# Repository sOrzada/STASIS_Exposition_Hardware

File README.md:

# STASIS_Exposure_Hardware
This is the repository for the exposure hardware of the STASIS project.
The corresponding software can be found in this repository: https://github.com/sOrzada/STASIS_Control

by Stephan Orzada @ German Cancer Research Center (DKFZ) 

# Overview
The STASIS RF exposure system is an open-source hardware and software platform designed for implant testing under exposure to radiofrequency (RF) fields, such as those encountered in the environment of an MRI system. For this purpose, the target RF frequency is 128 MHz, corresponding to the resonant frequency of protons in a 3 Tesla magnetic field. The system is capable of transmitting on eight independent RF channels, enabling parallel transmission.
To ensure the design is easily accessible to potential users, all design files and software are publicly available and can be accessed via the following repositories:
https://github.com/sOrzada/STASIS_Exposure_Hardware
https://github.com/sOrzada/STASIS_Control
All hardware components of the exposure system are licensed under the CERN-OHL-W while the software is licensed under a GNU GPL v3. In addition the project has been submitted to the conformity assessment body of the Open Source Imaging Initiative e.V. (https://www.opensourceimaging.org) to assess its open source status according to DIN SPEC 3105.  
To further improve accessibility, standard components with long production lifespans were selected wherever possible. For example, standard logic components were used instead of specialised microcontrollers or FPGAs.

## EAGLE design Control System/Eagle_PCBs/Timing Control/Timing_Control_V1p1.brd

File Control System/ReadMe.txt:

This Folder contains the PCBs and Housings for the Control System of the STASIS project's RF exposition system.
The PCBs are provided in two different formats: Eagle and KiCAD.
The Housings-folder contains .step files for the housings and front panels of the Eurocards.

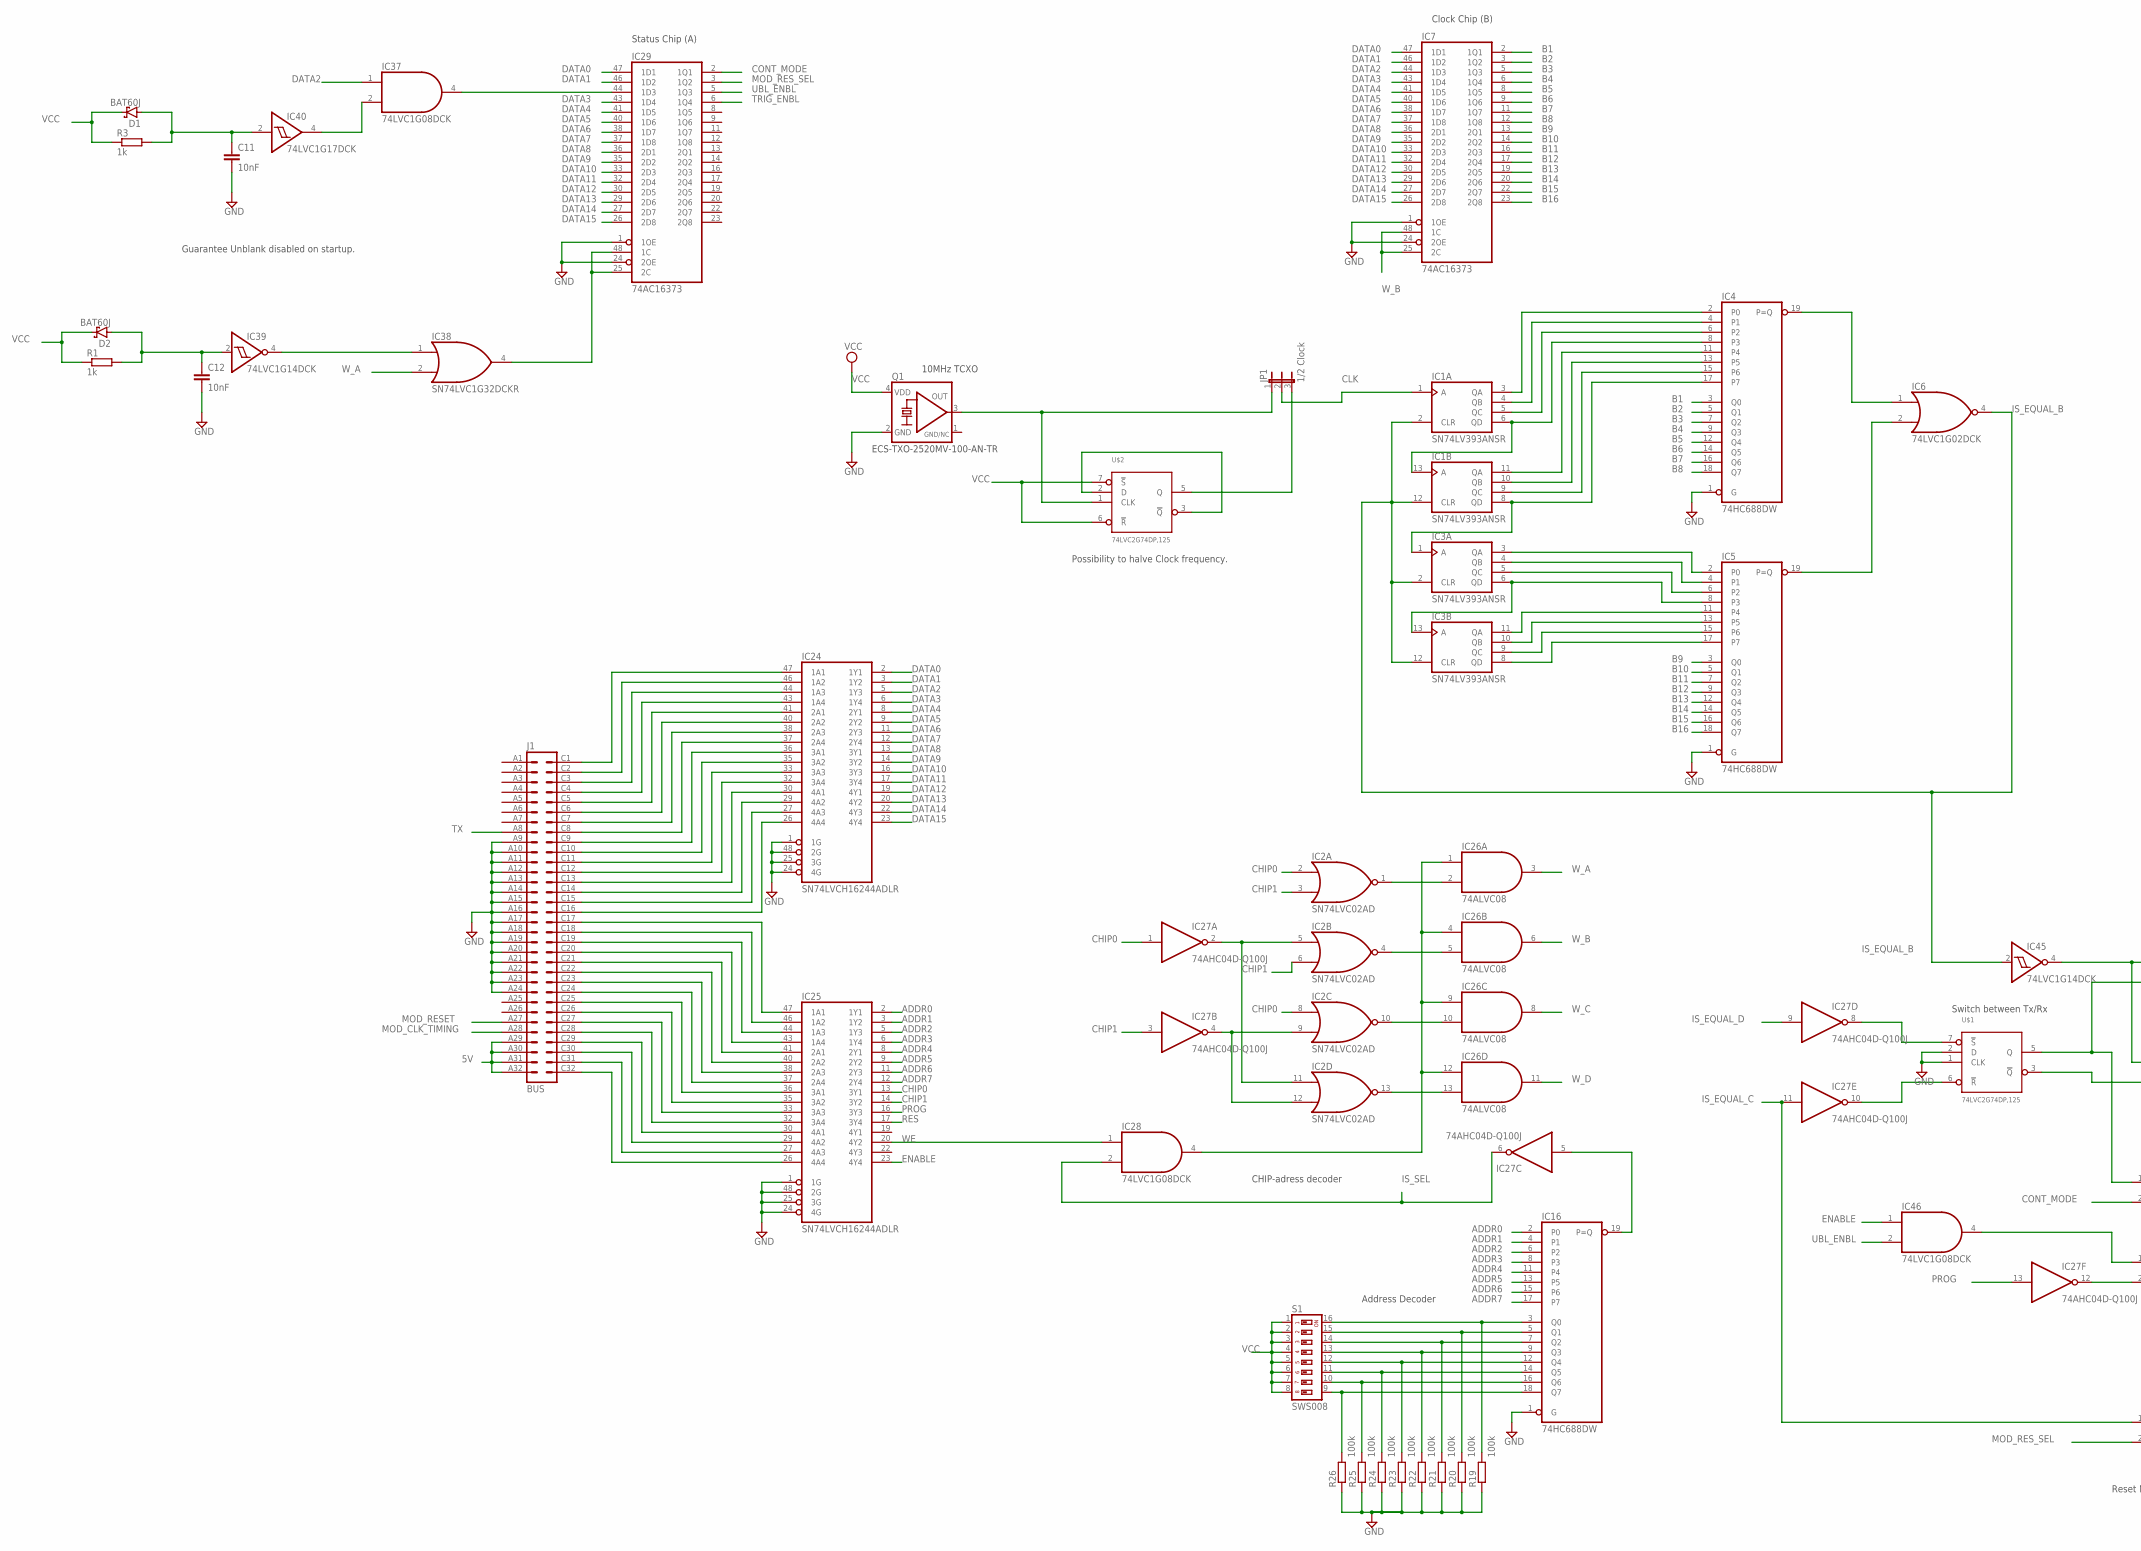
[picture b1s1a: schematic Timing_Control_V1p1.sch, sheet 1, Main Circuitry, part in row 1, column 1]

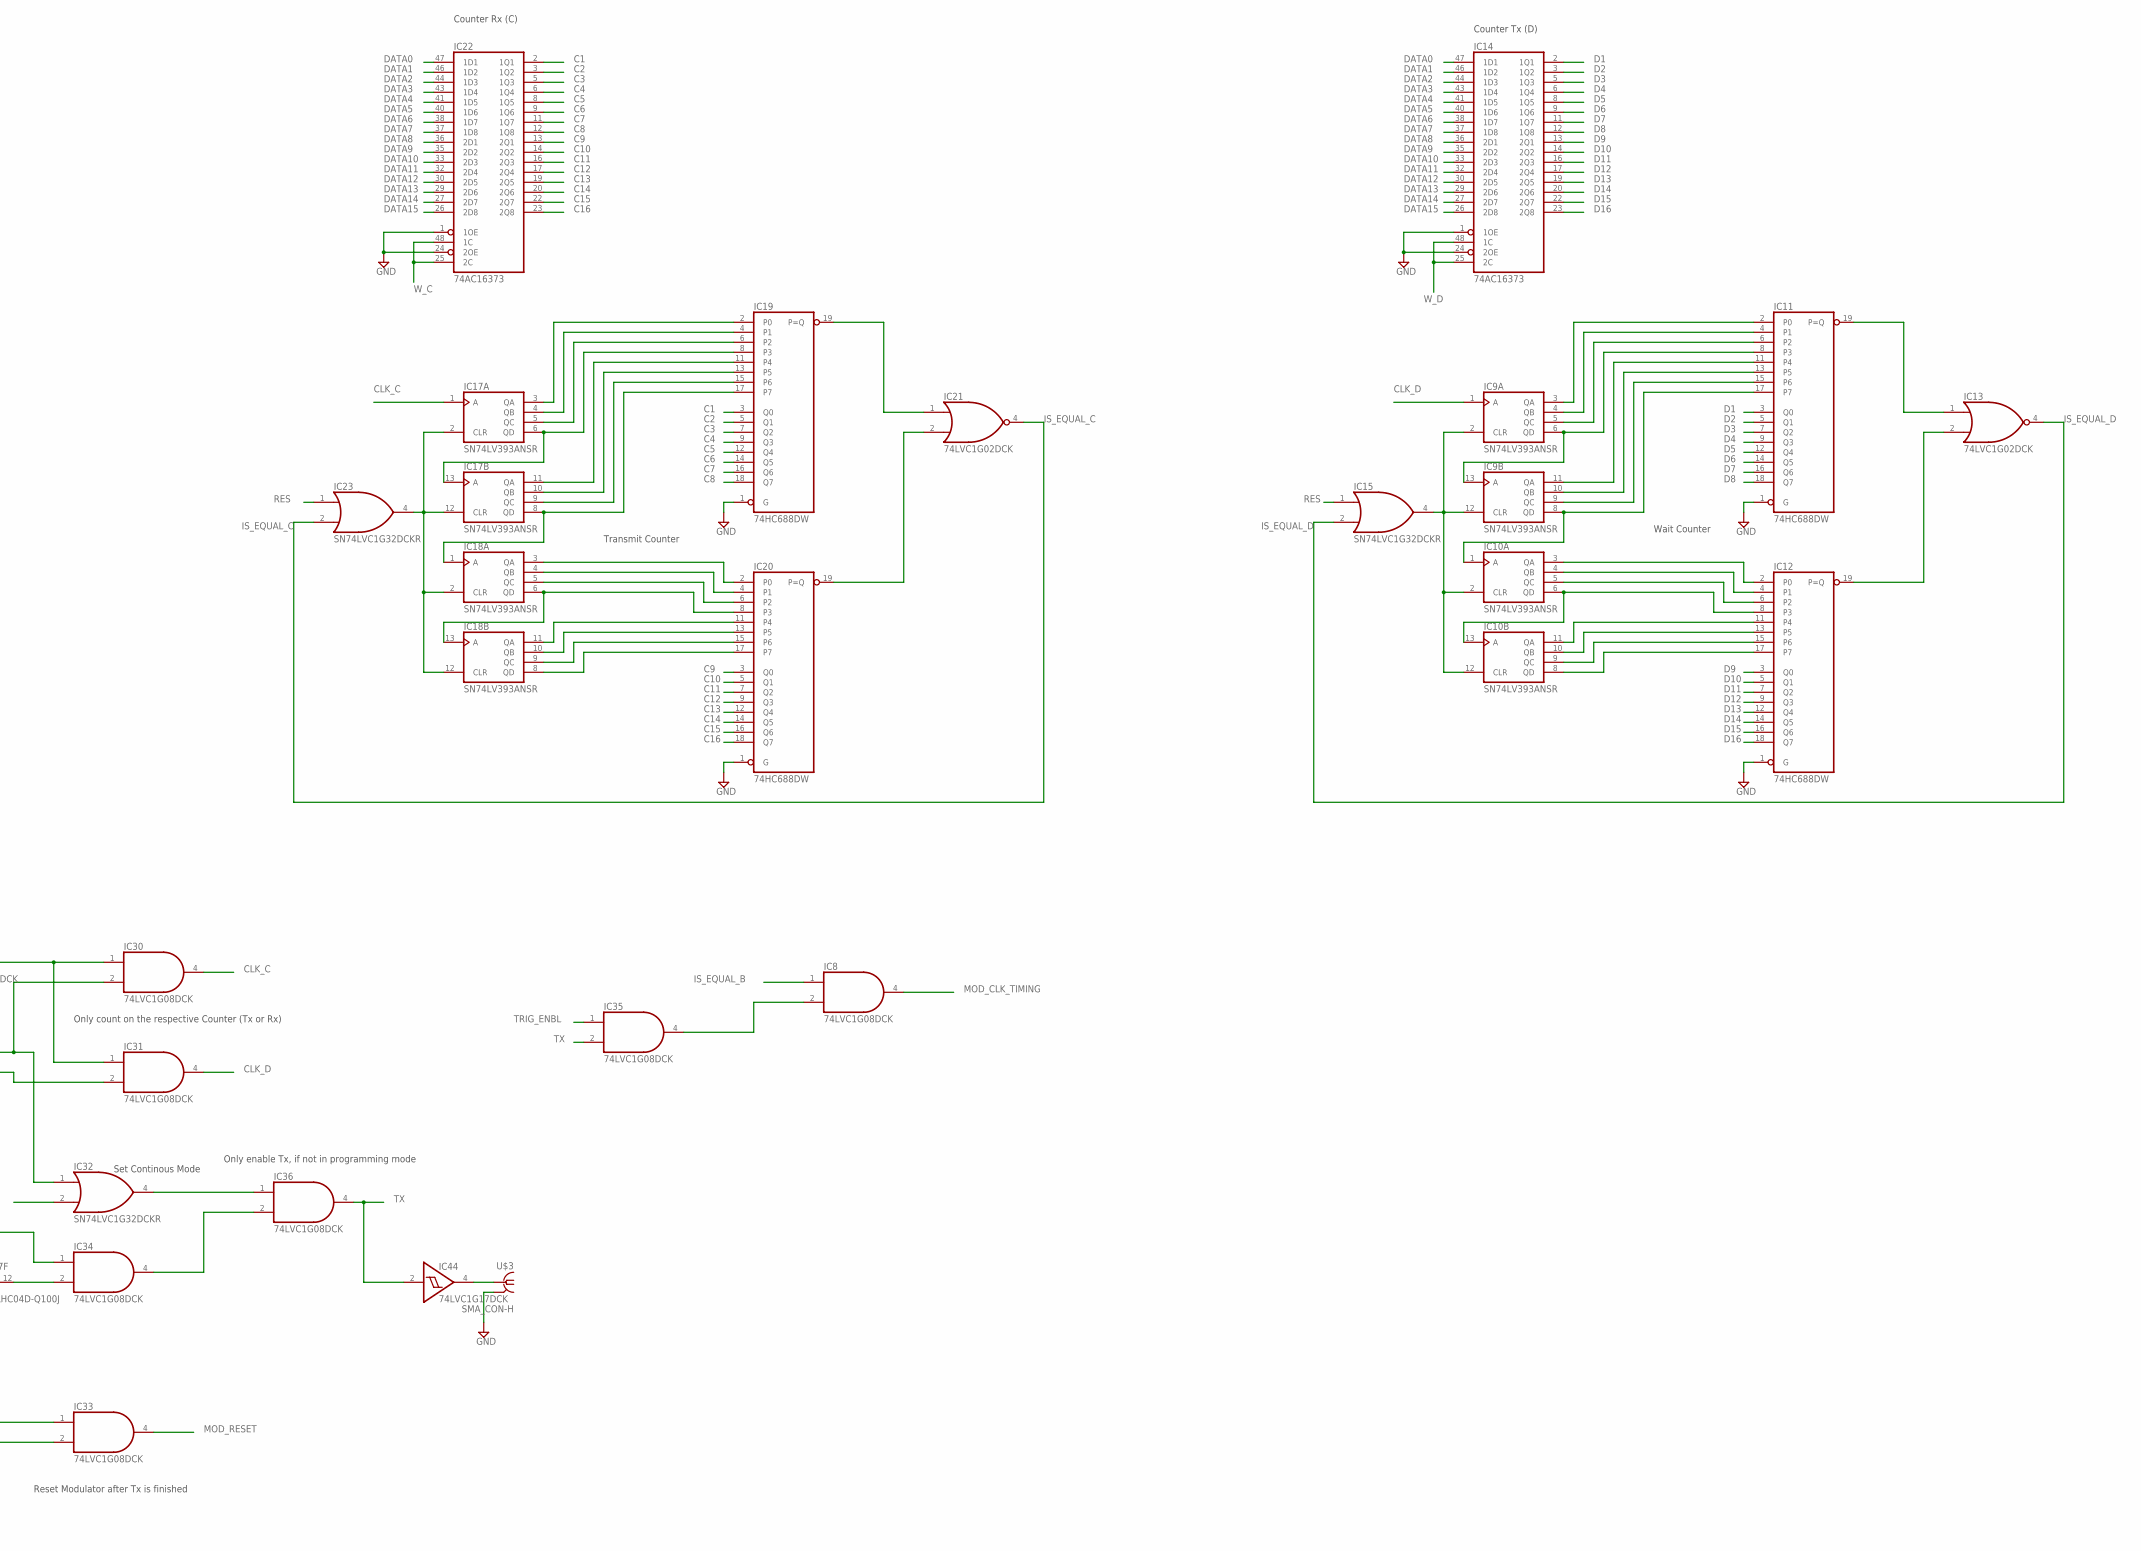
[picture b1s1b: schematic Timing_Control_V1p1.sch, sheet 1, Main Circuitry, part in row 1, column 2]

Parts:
C11, C12: 10nF; C0603
D1, D2: BAT60J; SOD323_ST
IC1, IC3, IC9, IC10, IC17, IC18: SN74LV393ANSR; SO14
IC2: SN74LVC02AD; SO14
IC4, IC5, IC11, IC12, IC16, IC19, IC20: 74HC688DW; SO20W
IC6, IC13, IC21: 74LVC1G02DCK; SC70-5
IC7, IC14, IC22, IC29: 74AC16373; SSOP48DL
IC8, IC28, IC30, IC31, IC33, IC34, IC35, IC36, IC37, IC46: 74LVC1G08DCK; SC70-5
IC15, IC23, IC32, IC38: SN74LVC1G32DCKR; SC70-5
IC24, IC25: SN74LVCH16244ADLR; SSOP48DL
IC26: 74ALVC08; SO14
IC27: 74AHC04D-Q100J; SO14
IC39, IC45: 74LVC1G14DCK; SC70-5
IC40, IC44: 74LVC1G17DCK; SC70-5
J1: BUS; VG64P
JP1: 1/2 Clock; JP2
Q1: ECS-TXO-2520MV-100-AN-TR; 2.5X2.0_KXO-86-TCXO
R1, R3: 1k; R0603
R19, R20, R21, R22, R23, R24, R25, R26: 100k; R0603
S1: SWS008; SMS-008
U$1, U$2: 74LVC2G74DP,125; SSOP08
U$3: SMA_CON-H; BU-SMA-H

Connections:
5V: J1.A29, J1.A30, J1.A31, J1.A32; also elsewhere on the board
ADDR0: IC16.2 (P0), IC25.2 (1Y1)
ADDR1: IC16.4 (P1), IC25.3 (1Y2)
ADDR2: IC16.6 (P2), IC25.5 (1Y3)
ADDR3: IC16.8 (P3), IC25.6 (1Y4)
ADDR4: IC16.11 (P4), IC25.8 (2Y1)
ADDR5: IC16.13 (P5), IC25.9 (2Y2)
ADDR6: IC16.15 (P6), IC25.11 (2Y3)
ADDR7: IC16.17 (P7), IC25.12 (2Y4)
B1: IC4.3 (Q0), IC7.2 (1Q1)
B2: IC4.5 (Q1), IC7.3 (1Q2)
B3: IC4.7 (Q2), IC7.5 (1Q3)
B4: IC4.9 (Q3), IC7.6 (1Q4)
B5: IC4.12 (Q4), IC7.8 (1Q5)
B6: IC4.14 (Q5), IC7.9 (1Q6)
B7: IC4.16 (Q6), IC7.11 (1Q7)
B8: IC4.18 (Q7), IC7.12 (1Q8)
B9: IC5.3 (Q0), IC7.13 (2Q1)
B10: IC5.5 (Q1), IC7.14 (2Q2)
B11: IC5.7 (Q2), IC7.16 (2Q3)
B12: IC5.9 (Q3), IC7.17 (2Q4)
B13: IC5.12 (Q4), IC7.19 (2Q5)
B14: IC5.14 (Q5), IC7.20 (2Q6)
B15: IC5.16 (Q6), IC7.22 (2Q7)
B16: IC5.18 (Q7), IC7.23 (2Q8)
C1: IC19.3 (Q0), IC22.2 (1Q1)
C2: IC19.5 (Q1), IC22.3 (1Q2)
C3: IC19.7 (Q2), IC22.5 (1Q3)
C4: IC19.9 (Q3), IC22.6 (1Q4)
C5: IC19.12 (Q4), IC22.8 (1Q5)
C6: IC19.14 (Q5), IC22.9 (1Q6)
C7: IC19.16 (Q6), IC22.11 (1Q7)
C8: IC19.18 (Q7), IC22.12 (1Q8)
C9: IC20.3 (Q0), IC22.13 (2Q1)
C10: IC20.5 (Q1), IC22.14 (2Q2)
C11: IC20.7 (Q2), IC22.16 (2Q3)
C12: IC20.9 (Q3), IC22.17 (2Q4)
C13: IC20.12 (Q4), IC22.19 (2Q5)
C14: IC20.14 (Q5), IC22.20 (2Q6)
C15: IC20.16 (Q6), IC22.22 (2Q7)
C16: IC20.18 (Q7), IC22.23 (2Q8)
CHIP0: IC2.2 (I0), IC2.8 (I0), IC25.13 (3Y1), IC27.1 (I)
CHIP1: IC2.3 (I1), IC2.6 (I1), IC25.14 (3Y2), IC27.3 (I)
CLK: IC1.1 (A), JP1.2
CLK_C: IC17.1 (A), IC30.4 (O)
CLK_D: IC9.1 (A), IC31.4 (O)
CLR1: IC9.2 (CLR), IC9.12 (CLR), IC10.2 (CLR), IC10.12 (CLR), IC15.4 (O)
CLR2: IC17.2 (CLR), IC17.12 (CLR), IC18.2 (CLR), IC18.12 (CLR), IC23.4 (O)
CONT_MODE: IC29.2 (1Q1), IC32.2 (I1); also elsewhere on the board
D1: IC11.3 (Q0), IC14.2 (1Q1)
D2: IC11.5 (Q1), IC14.3 (1Q2)
D3: IC11.7 (Q2), IC14.5 (1Q3)
D4: IC11.9 (Q3), IC14.6 (1Q4)
D5: IC11.12 (Q4), IC14.8 (1Q5)
D6: IC11.14 (Q5), IC14.9 (1Q6)
D7: IC11.16 (Q6), IC14.11 (1Q7)
D8: IC11.18 (Q7), IC14.12 (1Q8)
D9: IC12.3 (Q0), IC14.13 (2Q1)
D10: IC12.5 (Q1), IC14.14 (2Q2)
D11: IC12.7 (Q2), IC14.16 (2Q3)
D12: IC12.9 (Q3), IC14.17 (2Q4)
D13: IC12.12 (Q4), IC14.19 (2Q5)
D14: IC12.14 (Q5), IC14.20 (2Q6)
D15: IC12.16 (Q6), IC14.22 (2Q7)
D16: IC12.18 (Q7), IC14.23 (2Q8)
DATA0: IC7.47 (1D1), IC14.47 (1D1), IC22.47 (1D1), IC24.2 (1Y1), IC29.47 (1D1)
DATA1: IC7.46 (1D2), IC14.46 (1D2), IC22.46 (1D2), IC24.3 (1Y2), IC29.46 (1D2)
DATA2: IC7.44 (1D3), IC14.44 (1D3), IC22.44 (1D3), IC24.5 (1Y3), IC37.1 (I0)
DATA3: IC7.43 (1D4), IC14.43 (1D4), IC22.43 (1D4), IC24.6 (1Y4), IC29.43 (1D4)
DATA4: IC7.41 (1D5), IC14.41 (1D5), IC22.41 (1D5), IC24.8 (2Y1), IC29.41 (1D5)
DATA5: IC7.40 (1D6), IC14.40 (1D6), IC22.40 (1D6), IC24.9 (2Y2), IC29.40 (1D6)
DATA6: IC7.38 (1D7), IC14.38 (1D7), IC22.38 (1D7), IC24.11 (2Y3), IC29.38 (1D7)
DATA7: IC7.37 (1D8), IC14.37 (1D8), IC22.37 (1D8), IC24.12 (2Y4), IC29.37 (1D8)
DATA8: IC7.36 (2D1), IC14.36 (2D1), IC22.36 (2D1), IC24.13 (3Y1), IC29.36 (2D1)
DATA9: IC7.35 (2D2), IC14.35 (2D2), IC22.35 (2D2), IC24.14 (3Y2), IC29.35 (2D2)
DATA10: IC7.33 (2D3), IC14.33 (2D3), IC22.33 (2D3), IC24.16 (3Y3), IC29.33 (2D3)
DATA11: IC7.32 (2D4), IC14.32 (2D4), IC22.32 (2D4), IC24.17 (3Y4), IC29.32 (2D4)
DATA12: IC7.30 (2D5), IC14.30 (2D5), IC22.30 (2D5), IC24.19 (4Y1), IC29.30 (2D5)
DATA13: IC7.29 (2D6), IC14.29 (2D6), IC22.29 (2D6), IC24.20 (4Y2), IC29.29 (2D6)
DATA14: IC7.27 (2D7), IC14.27 (2D7), IC22.27 (2D7), IC24.22 (4Y3), IC29.27 (2D7)
DATA15: IC7.26 (2D8), IC14.26 (2D8), IC22.26 (2D8), IC24.23 (4Y4), IC29.26 (2D8)
ENABLE: IC25.23 (4Y4), IC46.1 (I0)
GND: C11.2, C12.2, IC1.7 (GND), IC2.7 (GND), IC3.7 (GND), IC4.1 (G), IC4.10 (GND), IC5.1 (G), IC5.10 (GND), IC6.3 (GND), IC7.1 (1OE), IC7.4 (GND), IC7.10 (GND), IC7.15 (GND), IC7.21 (GND), IC7.24 (2OE), IC7.28 (GND), IC7.34 (GND), IC7.39 (GND), IC7.45 (GND), IC8.3 (GND), IC9.7 (GND), IC10.7 (GND), IC11.1 (G), IC11.10 (GND), IC12.1 (G), IC12.10 (GND), IC13.3 (GND), IC14.1 (1OE), IC14.4 (GND), IC14.10 (GND), IC14.15 (GND), IC14.21 (GND), IC14.24 (2OE), IC14.28 (GND), IC14.34 (GND), IC14.39 (GND), IC14.45 (GND), IC15.3 (GND), IC16.1 (G), IC16.10 (GND), IC17.7 (GND), IC18.7 (GND), IC19.1 (G), IC19.10 (GND), IC20.1 (G), IC20.10 (GND), IC21.3 (GND), IC22.1 (1OE), IC22.4 (GND), IC22.10 (GND), IC22.15 (GND), IC22.21 (GND), IC22.24 (2OE), IC22.28 (GND), IC22.34 (GND), IC22.39 (GND), IC22.45 (GND), IC23.3 (GND), IC24.1 (1G), IC24.4 (GND), IC24.10 (GND), IC24.15 (GND), IC24.21 (GND), IC24.24 (4G), IC24.25 (3G), IC24.28 (GND), IC24.34 (GND), IC24.39 (GND), IC24.45 (GND), IC24.48 (2G), IC25.1 (1G), IC25.4 (GND), IC25.10 (GND), IC25.15 (GND), IC25.21 (GND), IC25.24 (4G), IC25.25 (3G), IC25.28 (GND), IC25.34 (GND), IC25.39 (GND), IC25.45 (GND), IC25.48 (2G), IC26.7 (GND), IC27.7 (GND), IC28.3 (GND), IC29.1 (1OE), IC29.4 (GND), IC29.10 (GND), IC29.15 (GND), IC29.21 (GND), IC29.24 (2OE), IC29.28 (GND), IC29.34 (GND), IC29.39 (GND), IC29.45 (GND), IC30.3 (GND), IC31.3 (GND), IC32.3 (GND), IC33.3 (GND), IC34.3 (GND), IC35.3 (GND), IC36.3 (GND), IC37.3 (GND), IC38.3 (GND), IC39.3 (GND), IC40.3 (GND), IC44.3 (GND), IC45.3 (GND), IC46.3 (GND), J1.A9, J1.A10, J1.A11, J1.A12, J1.A13, J1.A14, J1.A15, J1.A16, J1.A17, J1.A18, J1.A19, J1.A20, J1.A21, J1.A22, J1.A23, J1.A24, Q1.2 (GND), R19.1, R20.1, R21.1, R22.1, R23.1, R24.1, R25.1, R26.1, U$1.1 (CLK), U$1.2 (D), U$1.4 (GND), U$2.4 (GND), U$3.2 (GND), U$3.3 (GND), U$3.4 (GND), U$3.5 (GND); also elsewhere on the board
GND/NC: Q1.1 (GND/NC)
IS_EQUAL_B: IC1.2 (CLR), IC1.12 (CLR), IC3.2 (CLR), IC3.12 (CLR), IC6.4 (O), IC8.1 (I0), IC45.2 (I)
IS_EQUAL_C: IC21.4 (O), IC23.2 (I1), IC27.11 (I), IC33.1 (I0)
IS_EQUAL_D: IC13.4 (O), IC15.2 (I1), IC27.9 (I)
IS_SEL: IC27.6 (O), IC28.2 (I1); also elsewhere on the board
MOD_CLK_TIMING: IC8.4 (O), J1.A28
MOD_RESET: IC33.4 (O), J1.A27
MOD_RES_SEL: IC29.3 (1Q2), IC33.2 (I1)
unnamed: IC1.6 (QD), IC1.13 (A), IC4.8 (P3)
unnamed: IC1.8 (QD), IC3.1 (A), IC4.17 (P7)
unnamed: IC3.6 (QD), IC3.13 (A), IC5.8 (P3)
unnamed: IC8.2 (I1), IC35.4 (O)
unnamed: IC1.3 (QA), IC4.2 (P0)
unnamed: IC1.4 (QB), IC4.4 (P1)
unnamed: IC1.5 (QC), IC4.6 (P2)
unnamed: IC1.11 (QA), IC4.11 (P4)
unnamed: IC1.10 (QB), IC4.13 (P5)
unnamed: IC1.9 (QC), IC4.15 (P6)
unnamed: IC3.3 (QA), IC5.2 (P0)
unnamed: IC3.4 (QB), IC5.4 (P1)
unnamed: IC3.5 (QC), IC5.6 (P2)
unnamed: IC9.6 (QD), IC9.13 (A), IC11.8 (P3)
unnamed: IC3.11 (QA), IC5.11 (P4)
unnamed: IC3.10 (QB), IC5.13 (P5)
unnamed: IC3.9 (QC), IC5.15 (P6)
unnamed: IC3.8 (QD), IC5.17 (P7)
unnamed: IC4.19 (P=Q), IC6.1 (I0)
unnamed: IC5.19 (P=Q), IC6.2 (I1)
unnamed: IC9.8 (QD), IC10.1 (A), IC11.17 (P7)
unnamed: IC10.6 (QD), IC10.13 (A), IC12.8 (P3)
unnamed: IC9.3 (QA), IC11.2 (P0)
unnamed: IC9.4 (QB), IC11.4 (P1)
unnamed: IC9.5 (QC), IC11.6 (P2)
unnamed: IC9.11 (QA), IC11.11 (P4)
unnamed: IC9.10 (QB), IC11.13 (P5)
unnamed: IC9.9 (QC), IC11.15 (P6)
unnamed: IC10.3 (QA), IC12.2 (P0)
unnamed: IC10.4 (QB), IC12.4 (P1)
unnamed: IC10.5 (QC), IC12.6 (P2)
unnamed: IC10.11 (QA), IC12.11 (P4)
unnamed: IC10.10 (QB), IC12.13 (P5)
unnamed: IC10.9 (QC), IC12.15 (P6)
unnamed: IC10.8 (QD), IC12.17 (P7)
unnamed: IC11.19 (P=Q), IC13.1 (I0)
unnamed: IC12.19 (P=Q), IC13.2 (I1)
unnamed: IC27.12 (O), IC34.2 (I1)
unnamed: IC17.6 (QD), IC17.13 (A), IC19.8 (P3)
unnamed: IC16.3 (Q0), R19.2, S1.16
unnamed: IC17.8 (QD), IC18.1 (A), IC19.17 (P7)
unnamed: IC18.6 (QD), IC18.13 (A), IC20.8 (P3)
unnamed: IC17.3 (QA), IC19.2 (P0)
unnamed: IC17.4 (QB), IC19.4 (P1)
unnamed: IC17.5 (QC), IC19.6 (P2)
unnamed: IC17.11 (QA), IC19.11 (P4)
unnamed: IC17.10 (QB), IC19.13 (P5)
unnamed: IC17.9 (QC), IC19.15 (P6)
unnamed: IC18.3 (QA), IC20.2 (P0)
unnamed: IC18.4 (QB), IC20.4 (P1)
unnamed: IC18.5 (QC), IC20.6 (P2)
unnamed: IC18.11 (QA), IC20.11 (P4)
unnamed: IC18.10 (QB), IC20.13 (P5)
unnamed: IC18.9 (QC), IC20.15 (P6)
unnamed: IC18.8 (QD), IC20.17 (P7)
unnamed: IC19.19 (P=Q), IC21.1 (I0)
unnamed: IC20.19 (P=Q), IC21.2 (I1)
unnamed: IC34.4 (O), IC36.2 (I1)
unnamed: IC24.47 (1A1), J1.C1
unnamed: IC24.46 (1A2), J1.C2
unnamed: IC24.44 (1A3), J1.C3
unnamed: IC24.43 (1A4), J1.C4
unnamed: IC24.41 (2A1), J1.C5
unnamed: IC16.5 (Q1), R20.2, S1.15
unnamed: IC16.7 (Q2), R21.2, S1.14
unnamed: IC16.9 (Q3), R22.2, S1.13
unnamed: IC16.12 (Q4), R23.2, S1.12
unnamed: IC16.14 (Q5), R24.2, S1.11
unnamed: IC16.16 (Q6), R25.2, S1.10
unnamed: IC16.18 (Q7), R26.2, S1.9
unnamed: IC24.40 (2A2), J1.C6
unnamed: IC24.38 (2A3), J1.C7
unnamed: IC24.37 (2A4), J1.C8
unnamed: IC24.36 (3A1), J1.C9
unnamed: IC24.35 (3A2), J1.C10
unnamed: IC24.33 (3A3), J1.C11
unnamed: IC24.32 (3A4), J1.C12
unnamed: IC24.30 (4A1), J1.C13
unnamed: IC24.29 (4A2), J1.C14
unnamed: IC16.19 (P=Q), IC27.5 (I)
unnamed: IC24.27 (4A3), J1.C15
unnamed: IC24.26 (4A4), J1.C16
unnamed: IC25.47 (1A1), J1.C17
unnamed: IC25.46 (1A2), J1.C18
unnamed: IC25.44 (1A3), J1.C19
unnamed: IC25.43 (1A4), J1.C20
unnamed: IC25.41 (2A1), J1.C21
unnamed: IC25.40 (2A2), J1.C22
unnamed: IC25.38 (2A3), J1.C23
unnamed: IC25.37 (2A4), J1.C24
unnamed: IC25.36 (3A1), J1.C25
unnamed: IC25.35 (3A2), J1.C26
unnamed: IC25.33 (3A3), J1.C27
unnamed: IC25.32 (3A4), J1.C28
unnamed: IC25.30 (4A1), J1.C29
unnamed: IC25.29 (4A2), J1.C30
unnamed: IC25.27 (4A3), J1.C31
unnamed: IC25.26 (4A4), J1.C32
unnamed: IC2.5 (I0), IC2.11 (I0), IC27.2 (O)
unnamed: IC2.9 (I1), IC2.12 (I1), IC27.4 (O)
unnamed: IC2.1 (O), IC26.2 (I1)
unnamed: IC2.4 (O), IC26.5 (I1)
unnamed: IC2.10 (O), IC26.10 (I1)
unnamed: IC2.13 (O), IC26.13 (I1)
unnamed: IC26.1 (I0), IC26.4 (I0), IC26.9 (I0), IC26.12 (I0), IC28.4 (O)
unnamed: IC30.2 (I1), IC32.1 (I0), U$1.5 (Q)
unnamed: IC31.2 (I1), U$1.3 (!Q)
unnamed: IC27.8 (O), U$1.7 (!S)
unnamed: IC27.10 (O), U$1.6 (!R)
unnamed: IC32.4 (O), IC36.1 (I0)
unnamed: JP1.1, Q1.3 (OUT), U$2.1 (CLK)
unnamed: IC29.44 (1D3), IC37.4 (O)
unnamed: U$2.2 (D), U$2.3 (!Q)
unnamed: JP1.3, U$2.5 (Q)
unnamed: IC29.25 (2C), IC29.48 (1C), IC38.4 (O)
unnamed: IC37.2 (I1), IC40.4 (O)
unnamed: C11.1, D1.A, IC40.2 (I), R3.2
unnamed: IC38.1 (I0), IC39.4 (O)
unnamed: C12.1, D2.A, IC39.2 (I), R1.2
unnamed: IC34.1 (I0), IC46.4 (O)
unnamed: IC44.4 (O), U$3.1
unnamed: IC30.1 (I0), IC31.1 (I0), IC45.4 (O)
PROG: IC25.16 (3Y3), IC27.13 (I)
RES: IC15.1 (I0), IC23.1 (I0), IC25.17 (3Y4)
TRIG_ENBL: IC29.6 (1Q4), IC35.1 (I0)
TX: IC35.2 (I1), IC36.4 (O), IC44.2 (I), J1.A8; also elsewhere on the board
UBL_ENBL: IC29.5 (1Q3), IC46.2 (I1)
VCC: D1.C, D2.C, IC1.14 (VCC), IC2.14 (VCC), IC3.14 (VCC), IC4.20 (VCC), IC5.20 (VCC), IC6.5 (VCC), IC7.7 (VCC), IC7.18 (VCC), IC7.31 (VCC), IC7.42 (VCC), IC8.5 (VCC), IC9.14 (VCC), IC10.14 (VCC), IC11.20 (VCC), IC12.20 (VCC), IC13.5 (VCC), IC14.7 (VCC), IC14.18 (VCC), IC14.31 (VCC), IC14.42 (VCC), IC15.5 (VCC), IC16.20 (VCC), IC17.14 (VCC), IC18.14 (VCC), IC19.20 (VCC), IC20.20 (VCC), IC21.5 (VCC), IC22.7 (VCC), IC22.18 (VCC), IC22.31 (VCC), IC22.42 (VCC), IC23.5 (VCC), IC24.7 (VCC), IC24.18 (VCC), IC24.31 (VCC), IC24.42 (VCC), IC25.7 (VCC), IC25.18 (VCC), IC25.31 (VCC), IC25.42 (VCC), IC26.14 (VCC), IC27.14 (VCC), IC28.5 (VCC), IC29.7 (VCC), IC29.18 (VCC), IC29.31 (VCC), IC29.42 (VCC), IC30.5 (VCC), IC31.5 (VCC), IC32.5 (VCC), IC33.5 (VCC), IC34.5 (VCC), IC35.5 (VCC), IC36.5 (VCC), IC37.5 (VCC), IC38.5 (VCC), IC39.5 (VCC), IC40.5 (VCC), IC44.5 (VCC), IC45.5 (VCC), IC46.5 (VCC), Q1.4 (VDD), R1.1, R3.1, S1.1, S1.2, S1.3, S1.4, S1.5, S1.6, S1.7, S1.8, U$1.8 (VCC), U$2.6 (!R), U$2.7 (!S), U$2.8 (VCC); also elsewhere on the board
WE: IC25.20 (4Y2), IC28.1 (I0)
W_A: IC26.3 (O), IC38.2 (I1)
W_B: IC7.25 (2C), IC7.48 (1C), IC26.6 (O)
W_C: IC22.25 (2C), IC22.48 (1C), IC26.8 (O)
W_D: IC14.25 (2C), IC14.48 (1C), IC26.11 (O)

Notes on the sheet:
Address Decoder
CHIP-adress decoder
Status Chip (A)
Clock Chip (B)
Counter Tx (D)
Counter Rx (C)
Reset Modulator after Tx is finished
Set Continous Mode
Switch between Tx/Rx
Only count on the respective Counter (Tx or Rx)
Only enable Tx, if not in programming mode
ECS-TXO-2520MV-100-AN-TR
10MHz TCXO
Possibility to halve Clock frequency.
Guarantee Unblank disabled on startup.
Transmit Counter
Wait Counter

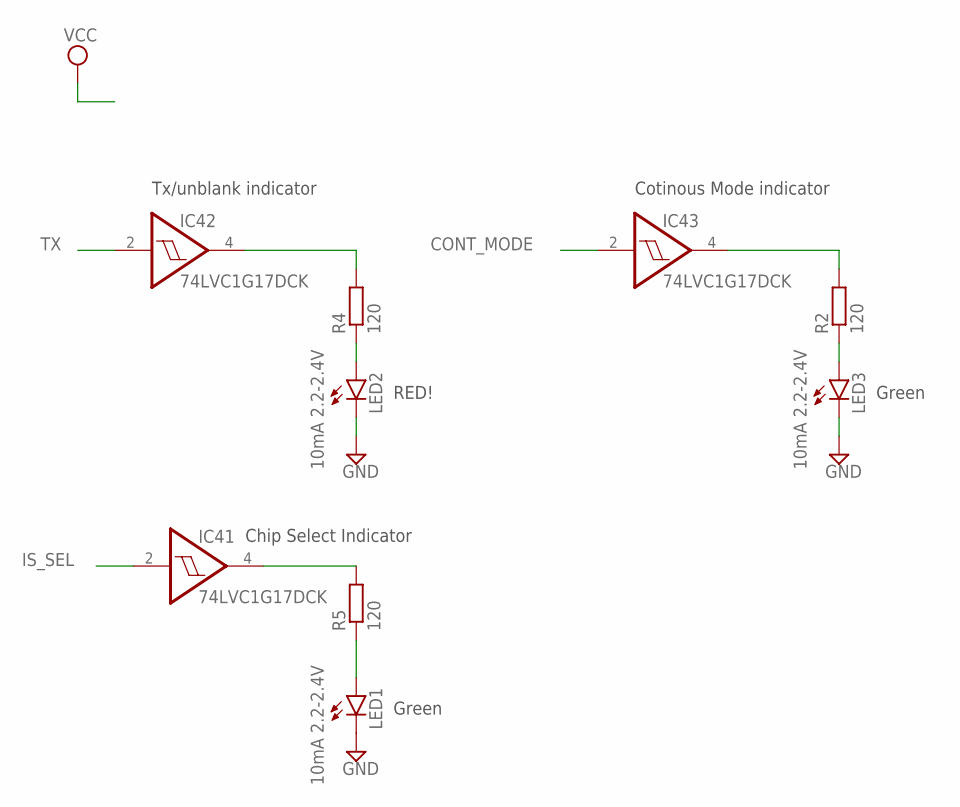
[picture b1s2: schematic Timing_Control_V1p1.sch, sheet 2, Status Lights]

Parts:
IC41, IC42, IC43: 74LVC1G17DCK; SC70-5
LED1, LED2, LED3: 10mA 2.2-2.4V; LED3MM
R2, R4, R5: 120; R0603

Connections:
CONT_MODE: IC43.2 (I); also elsewhere on the board
GND: IC41.3 (GND), IC42.3 (GND), IC43.3 (GND), LED1.K (C), LED2.K (C), LED3.K (C); also elsewhere on the board
IS_SEL: IC41.2 (I); also elsewhere on the board
unnamed: IC43.4 (O), R2.2
unnamed: IC41.4 (O), R5.2
unnamed: LED1.A, R5.1
unnamed: LED3.A, R2.1
unnamed: IC42.4 (O), R4.2
unnamed: LED2.A, R4.1
TX: IC42.2 (I); also elsewhere on the board
VCC: IC41.5 (VCC), IC42.5 (VCC), IC43.5 (VCC); also elsewhere on the board

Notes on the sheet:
Chip Select Indicator
RED!
Green
Tx/unblank indicator
Cotinous Mode indicator

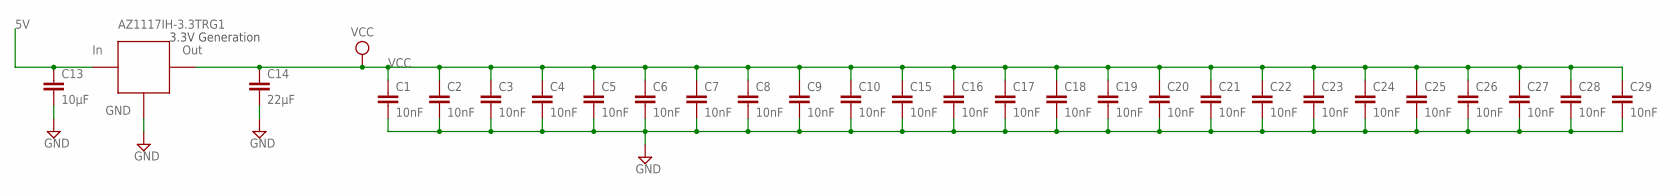
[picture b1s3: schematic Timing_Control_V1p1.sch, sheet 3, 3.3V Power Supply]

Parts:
C1, C2, C3, C4, C5, C6, C7, C8, C9, C10, C15, C16, C17, C18, C19, C20, C21, C22, C23, C24, C25, C26, C27, C28, C29: 10nF; C0603
C13: 10µF; C1206
C14: 22µF; C1206
U$9: AZ1117IH-3.3TRG1; SOT223

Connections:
5V: C13.1, U$9.3 (IN); also elsewhere on the board
GND: C1.2, C2.2, C3.2, C4.2, C5.2, C6.2, C7.2, C8.2, C9.2, C10.2, C13.2, C14.2, C15.2, C16.2, C17.2, C18.2, C19.2, C20.2, C21.2, C22.2, C23.2, C24.2, C25.2, C26.2, C27.2, C28.2, C29.2, U$9.1 (GND); also elsewhere on the board
VCC: C1.1, C2.1, C3.1, C4.1, C5.1, C6.1, C7.1, C8.1, C9.1, C10.1, C14.1, C15.1, C16.1, C17.1, C18.1, C19.1, C20.1, C21.1, C22.1, C23.1, C24.1, C25.1, C26.1, C27.1, C28.1, C29.1, U$9.2 (VCC), U$9.4 (VCC); also elsewhere on the board

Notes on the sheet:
3.3V Generation

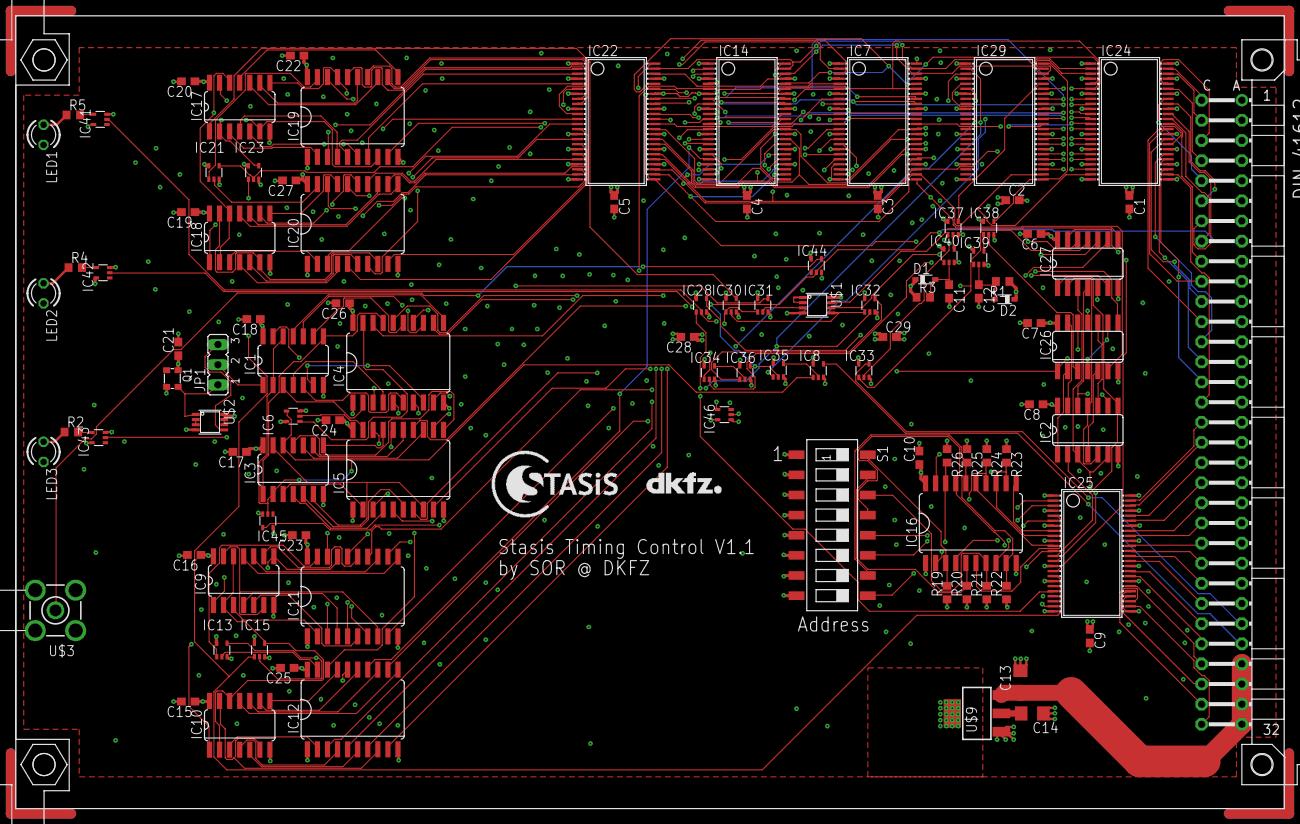
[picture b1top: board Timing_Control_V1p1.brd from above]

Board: 6 copper layers, 160.0 x 100.0 mm, 103 parts (0 on the bottom side), 229 nets.

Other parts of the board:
U$4: LOGO_STASIS
U$5: LOGO_DKFZ

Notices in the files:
parts and their libraries:
Wurth_EMC Components_WE-SHC: Copyright: Würth Elektronik
crystal-geyer_V1_0: Copyright: Geyer-Electronic
